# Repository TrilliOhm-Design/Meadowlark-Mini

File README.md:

# Meadowlark-Mini

Dual deploy programable flight computer for amature rocketry. Equipped with a beeper, physical interrupt, battery monitoring, three pyro channels, IMU, and Pressure sensor. The goal is to offer a feature rich controller that can fit inside a 29mm chassis with the creature comforts of modern controllers. The system is powered by an ESP32-C6 microcontroller.  

### Hardware Specs
* 10 to 1200 mbar operating range 
* +/- 2.5 mbar pressure error band
* +/- 0.012 mbar relative pressure accuracy
* +/- 32g accelerometer range
* +/- 2000 dps gyroscope
* embedded temperature compensation
* ~35mA operating consumption 
* Buzzer 80db
* 3 pyro channels
* Stable power supply (3-17V)

### Testing
- [x] Hardware validation
- [x] Firmware Initialized
- [ ] Test Functionallity
        - [x] Indicator light
        - [x] Pyro circuit
        - [x] Buzzer
        - [x] Pressure sensor
        - [x] IMU
        - [ ] Flight logs
        - [ ] HighPower supply
- [ ] Software endurance test
- [ ] Simulated flight test
- [ ] Passenger flight tests (collect data and tune triggers)
- [ ] Flight as main controller
- [ ] Flight as secondary controller

Repeat any tests until the controller passes with reliable behavior.

# Hardware

The board is laid out such it has pyro channels on top and bottom. With two pyro channels on one side and an enable pin on the other. On the other side of the board you have a JST PH connector for power input from a 2s battery. 

I also wanted easy mounting so the board is mounted using two M3 screws.
### [Hardware Details](https://github.com/colinhalebrown/Meadowlark-Mini/tree/main/Hardware)

# Software

The board is equipped with WIFI, Bluetooth, LoRa and Zigbee. The ESP32-C6 has a built in antenna and a u.FL plug that the user can switch between. 

### Pinout
| System          | Signal Type    | Label    | GPIO         | Verified |
| --------------- | -------------- | -------- | ------------ | -------- |
| Indicator LED   | Digital Output | D13      | GPIO13       | Y        |
| Buzzer          | Digital Output | A0       | GPIO26       | Y        |
| Battery Monior  | Analog Input   | A1       | AD1          | Y        |
| Pyro 1          | Digital Output | D12      | GPIO12       | Y        |
| Pyro 2          | Digital Output | D3       | GPIO6        | Y        |
| Pyro 3          | Digital Output | D6       |              | Y        |
| Pressure Sensor | I2C            | SDA, SCL | GPIO2, GPIO3 | Y        |
| IMU             | I2C            | SDA, SCL | GPIO2, GPIO3 | Y        |

# Status
Currently the board needs software so it can get tested in flight as a payload.

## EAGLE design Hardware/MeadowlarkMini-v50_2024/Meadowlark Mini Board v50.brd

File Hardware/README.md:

# Meadowlark-Mini Hardware

### Known Issues
* none

Boards have paste added using a stencil

Components are added to the board by hand 

The board is then baked and the solder joints inspected. Board tested for shorts. After testing the board either needs rework or is cleared for a microcontroller. The controller and power plug are soldiered by hand to the bottom.

The boards are then tested and conformal coated once all rework as been completed. Ports, Plugs, buttons, and sensors are avoided to prevent loss of functionality. 

The enclosure was removed to save weight and allow for users to incorporate the board into their AV bays easier.

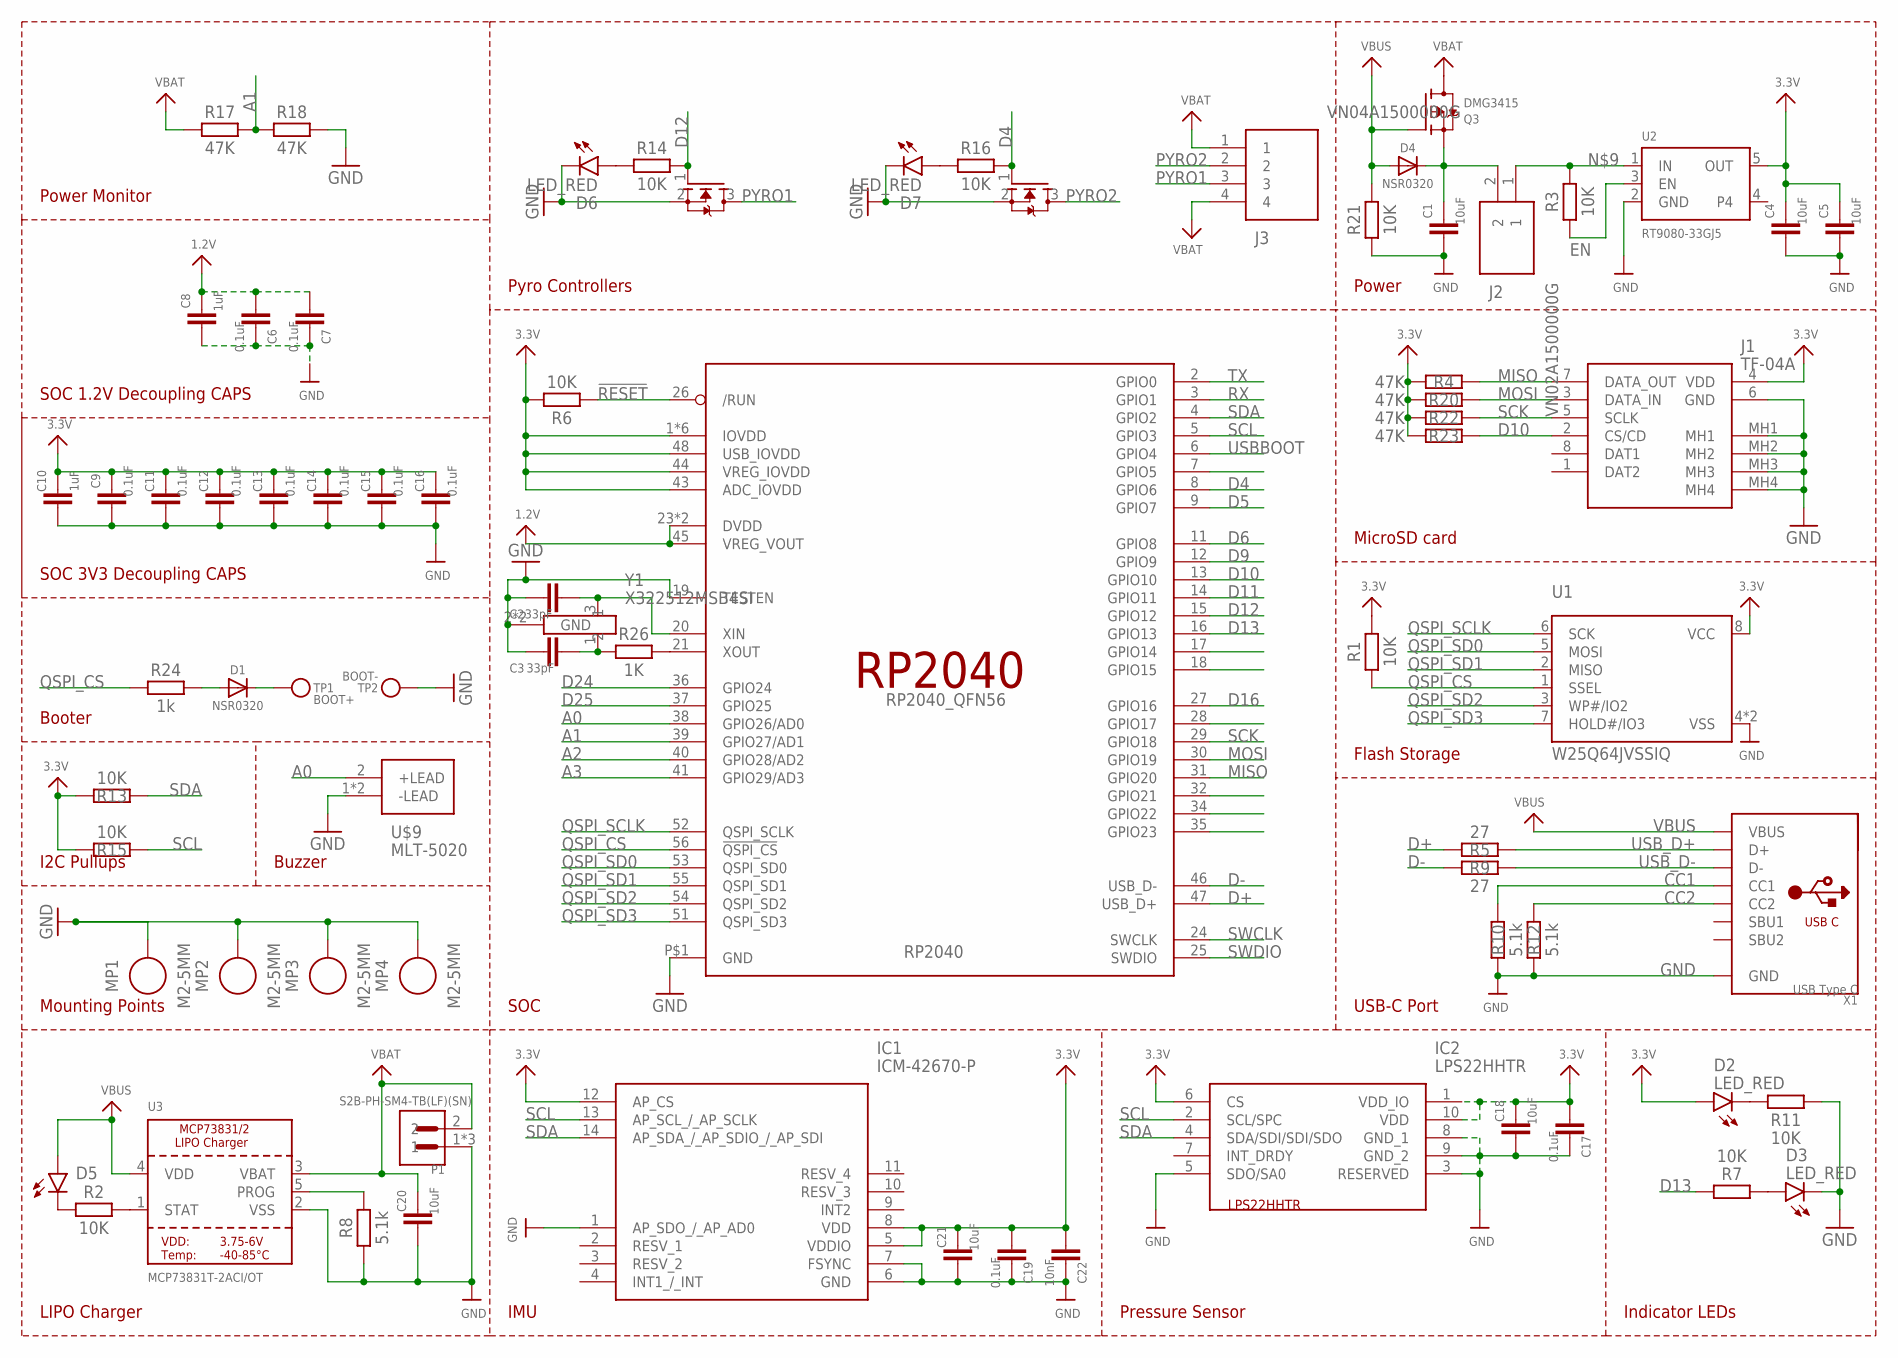
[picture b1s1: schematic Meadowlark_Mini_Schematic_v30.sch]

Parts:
C1, C4, C5, C18, C20, C21: 10uF; CAPC1005X60
C2, C3: 33pF; CAPC1005X60
C6, C7, C9, C11, C12, C13, C14, C15, C16, C17, C19: 0.1uF; CAPC1005X60
C8, C10: 1uF; CAPC1005X60
C22: 10nF; CAPC1005X60
D1, D4: NSR0320; SOD-323_MINI
D2, D3, D6, D7: LED_RED; LEDC1608X55N_FLAT-R
D5: LED_YELLOW; LEDC1608X55N_FLAT-Y
IC1: ICM-42670-P; ICM42670P
IC2: LPS22HHTR
J1: TF-04A; TF04A
J2: VN02A1500000G
J3: VN04A1500000G
MP1, MP2, MP3, MP4: M2-5MM; STANDOFF_HEX_MALE-FEMALE_400X500_M2X0.4_MTGP600H220
P1: S2B-PH-SM4-TB(LF)(SN); JST_S2B-PH-SM4-TB(LF)(SN)
Q1, Q2: AO3400A; SOT23-WIDE
Q3: DMG3415; SOT23-R
R1, R2, R3, R6, R7, R11, R13, R14, R15, R16, R21: 10K; RESC1005X40
R4, R17, R18, R20, R22, R23: 47K; RESC1005X40
R5, R9: 27; RESC1005X40
R8, R10, R12: 5.1k; RESC1005X40
R24: 1k; RESC1005X40
R26: 1K; RESC1005X40
RP2040: RP2040_QFN56; QFN56_7MM_REDUCEDEPAD
TP1: BOOT+; TESTPOINT_ROUND_1.5MM_NO
TP2: BOOT-; TESTPOINT_ROUND_1.5MM_NO
U1: W25Q64JVSSIQ; USON8_4X4
U2: RT9080-33GJ5; SOT23-5; JLC_ROTATION 0
U3: MCP73831T-2ACI/OT; SOT23-5
U$9: MLT-5020; MLT5020
X1: USB Type C; USB_C_CUSB31-CFM2AX-01-X
Y1: X322512MSB4SI

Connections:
1.2V: C6.2, C7.2, C8.1, RP2040.23 (DVDD), RP2040.45 (VREG_VOUT), RP2040.50 (DVDD)
3.3V: C4.1, C5.1, C9.1, C10.1, C11.1, C12.1, C13.1, C14.1, C15.1, C16.1, C17.2, C18.1, C19.2, C21.1, C22.2, D2.A, IC1.5 (VDDIO), IC1.8 (VDD), IC1.12 (AP_CS), IC2.1 (VDD_IO), IC2.6 (CS), IC2.10 (VDD), J1.4 (VDD), R1.2, R4.1, R6.2, R13.2, R15.2, R20.1, R22.1, R23.1, RP2040.1 (IOVDD), RP2040.10 (IOVDD), RP2040.22 (IOVDD), RP2040.33 (IOVDD), RP2040.42 (IOVDD), RP2040.43 (ADC_IOVDD), RP2040.44 (VREG_IOVDD), RP2040.48 (USB_IOVDD), RP2040.49 (IOVDD), U1.8 (VCC), U2.5 (OUT)
!RESET: R6.1, RP2040.26 (/RUN)
A0: RP2040.38 (GPIO26/AD0), U$9.2 (+LEAD)
A1: R17.2, R18.1, RP2040.39 (GPIO27/AD1)
A2: RP2040.40 (GPIO28/AD2)
A3: RP2040.41 (GPIO29/AD3)
CC1: R10.2, X1.A5 (CC1)
CC2: R12.2, X1.B5 (CC2)
D4: Q2.1 (G), R16.2, RP2040.8 (GPIO6)
D5: RP2040.9 (GPIO7)
D6: RP2040.11 (GPIO8)
D9: RP2040.12 (GPIO9)
D10: J1.2 (CS/CD), R23.2, RP2040.13 (GPIO10)
D11: RP2040.14 (GPIO11)
D12: Q1.1 (G), R14.2, RP2040.15 (GPIO12)
D13: R7.2, RP2040.16 (GPIO13)
D16: RP2040.27 (GPIO16)
D24: RP2040.36 (GPIO24)
D25: RP2040.37 (GPIO25)
D+: R5.1, RP2040.47 (USB_D+)
D-: R9.1, RP2040.46 (USB_D-)
EN: R3.1, U2.3 (EN)
GND: C1.2, C2.1, C3.1, C4.2, C5.2, C6.1, C7.1, C8.2, C9.2, C10.2, C11.2, C12.2, C13.2, C14.2, C15.2, C16.2, C17.1, C18.2, C19.1, C20.2, C21.2, C22.1, D3.C, D6.C, D7.C, IC1.1 (AP_SDO_/_AP_AD0), IC1.6 (GND), IC1.7 (FSYNC), IC2.3 (RESERVED), IC2.5 (SDO/SA0), IC2.8 (GND_1), IC2.9 (GND_2), J1.6 (GND), J1.MH1, J1.MH2, J1.MH3, J1.MH4, MP1.1, MP2.1, MP3.1, MP4.1, P1.1, P1.P1 (1), P1.P2 (1), Q1.2 (S), Q2.2 (S), R8.1, R10.1, R11.2, R12.1, R18.2, R21.1, RP2040.19 (TESTEN), RP2040.P$1 (GND), TP2.P$1, U1.4 (VSS), U1.PAD (VSS), U2.2 (GND), U3.2 (VSS), U$9.1 (-LEAD), U$9.3 (-LEAD), X1.A1B12 (GND), X1.B1A12 (GND), Y1.2 (GND), Y1.4 (GND)
MISO: J1.7 (DATA_OUT), R4.2, RP2040.31 (GPIO20)
MOSI: J1.3 (DATA_IN), R20.2, RP2040.30 (GPIO19)
unnamed: D5.C, R2.1
unnamed: D2.C, R11.1
unnamed: R2.2, U3.1 (STAT)
unnamed: R8.2, U3.5 (PROG)
unnamed: D6.A, R14.1
unnamed: C3.2, R26.1, Y1.1
unnamed: R26.2, RP2040.21 (XOUT)
unnamed: D1.A, R24.2
unnamed: J2.1, R3.2, U2.1 (IN)
unnamed: D3.A, R7.1
unnamed: D7.A, R16.1
unnamed: C2.2, RP2040.20 (XIN), Y1.3 (2)
PYRO1: J3.3, Q1.3 (D)
PYRO2: J3.2, Q2.3 (D)
QSPI_CS: R1.1, R24.1, RP2040.56 (!QSPI_CS), U1.1 (SSEL)
QSPI_SCLK: RP2040.52 (QSPI_SCLK), U1.6 (SCK)
QSPI_SD0: RP2040.53 (QSPI_SD0), U1.5 (MOSI)
QSPI_SD1: RP2040.55 (QSPI_SD1), U1.2 (MISO)
QSPI_SD2: RP2040.54 (QSPI_SD2), U1.3 (WP#/IO2)
QSPI_SD3: RP2040.51 (QSPI_SD3), U1.7 (HOLD#/IO3)
RX: RP2040.3 (GPIO1)
SCK: J1.5 (SCLK), R22.2, RP2040.29 (GPIO18)
SCL: IC1.13 (AP_SCL_/_AP_SCLK), IC2.2 (SCL/SPC), R15.1, RP2040.5 (GPIO3)
SDA: IC1.14 (AP_SDA_/_AP_SDIO_/_AP_SDI), IC2.4 (SDA/SDI/SDI/SDO), R13.1, RP2040.4 (GPIO2)
SWCLK: RP2040.24 (SWCLK)
SWDIO: RP2040.25 (SWDIO)
TX: RP2040.2 (GPIO0)
USBBOOT: D1.C, RP2040.6 (GPIO4), TP1.P$1
USB_D+: R5.2, X1.A6 (D+), X1.B6 (D+)
USB_D-: R9.2, X1.A7 (D-), X1.B7 (D-)
VBAT: C20.1, J3.1, J3.4, P1.2, Q3.3 (D), R17.1, U3.3 (VBAT)
VBUS: D4.A, D5.A, Q3.1 (G), R21.2, U3.4 (VDD), X1.A4B9 (VBUS), X1.B4A9 (VBUS)
VHI: C1.1, D4.C, J2.2, Q3.2 (S)

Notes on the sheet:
Power
LIPO Charger
MicroSD card
Flash Storage
USB-C Port
SOC
Pyro Controllers
IMU
Pressure Sensor
I2C Pullups
Indicator LEDs
Mounting Points
Buzzer
Booter
SOC 3V3 Decoupling CAPS
SOC 1.2V Decoupling CAPS
Power Monitor

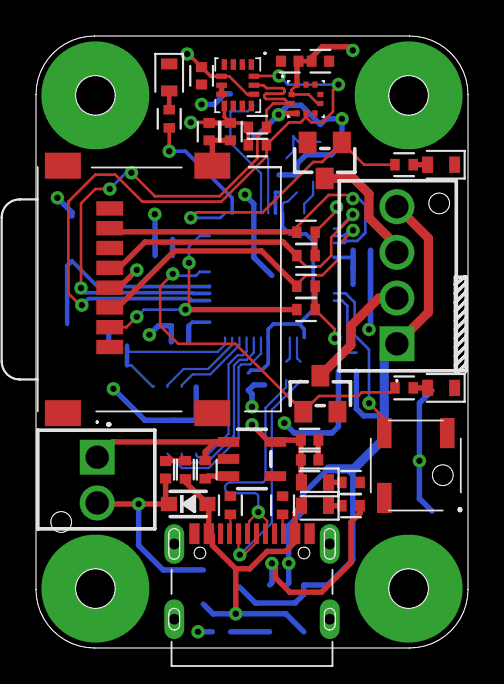
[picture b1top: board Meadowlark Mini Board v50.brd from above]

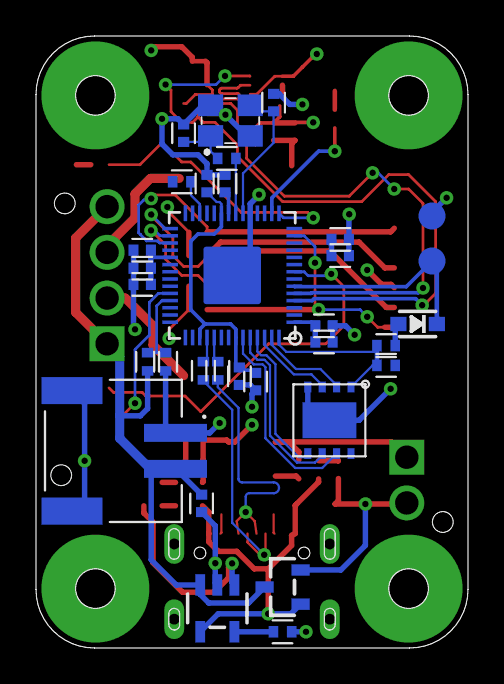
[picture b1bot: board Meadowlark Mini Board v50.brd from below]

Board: 2 copper layers, 24.0 x 34.0 mm, 75 parts (32 on the bottom side), 46 nets.

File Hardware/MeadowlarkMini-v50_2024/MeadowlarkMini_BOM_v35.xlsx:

Meadowlark Mini BOM
Comment | Designator | Footprint | Part # |  | URL | QTY | Type | Notes
MLT-5020 | U$9 | MLT5020 | C94598 |  | JLC | 1 | Extended | Buzzer
S2B-PH-SM4-TB | P1 | JST_S2B-PH-SM4-TB(LF)(SN) | C295747 |  | JLC | 1 | Extended | JST-PH 2P
RP2040 | RP2040 | QFN56_7MM_REDUCEDEPAD | C2040 |  | JLC | 1 | Extended | RP2040 SOC
TF-04A | J1 | TF04A | C145799 |  | JLC | 1 | Extended | MicroSD Slot
DB125-2.54-4P-GN-S | J3 | VN04A1500000G | C918122 |  | JLC | 1 | Extended | 4P 2.54mm Screw
DB301V-3.5-2P-GN-S | J2 | VN02A1500000G | C918120 |  | JLC | 1 | Extended | 2P 2.54mm Screw
W25Q64JVXGIQ | U1 | USON8_4X4 | C2940195 |  | JLC | 1 | Extended | Flash Storage
ICM-42670-P | IC1 | ICM42670P | C3288646 |  | JLC | 1 | Extended | IMU
LPS22HHTR | IC2 | LPS22HHTR | C2827824 |  | JLC | 1 | Extended | Barometer
SI2301CDS-T1-GE3 | Q3 | SOT23-R | C10487 |  | JLC | 1 | Basic | Power MOSFET
RT9080-33GJ5 | U2 | SOT23-5 | C841192 |  | JLC | 1 | Extended | Voltage regulator
MCP73831T-2ACI/OT | U3 | SOT23-5 | C424093 |  | JLC | 1 | Extended | LIPO Charger
TYPE-C 16PIN 2MD(073) | X1 | USB_C_CUSB31-CFM2AX-01-X | C2765186 |  | JLC | 1 | Extended | USB-C port
AO3400A | Q1, Q2 | SOT23-WIDE | C20917 |  | JLC | 2 | Basic | Load MOSFET
0402WGF1001TCE | R24, R26 | RESC1005X40 | C11702 |  | JLC | 2 | Basic | 1k 0402
1N5819WS | D1, D4 | SOD-323_MINI | C191023 |  | JLC | 2 | Basic | Original Part
0402WGF1002TCE | R1, R2, R3, R6, R7, R11, R13, R14, R15, R16, R21 | RESC1005X40 | C25744 |  | JLC | 13 | Basic | 10k 0402
CL05A106MQ5NUNC | C1, C4, C5, C18, C20, C21 | CAPC1005X60 | C15525 |  | JLC | 6 | Basic | 10uF 0402
CL05B104KB54PNC | C6, C7, C9, C11, C12, C13, C14, C15, C16, C17, C19 | CAPC1005X60 | C307331 |  | JLC | 11 | Basic | 0.1uF 0402
CL05B103KB5NNNC | C22 | CAPC1005X60 | C15195 |  | JLC | 1 | Basic | 10nF 0402
KT-0603R | D2, D3, D6, D7 | LEDC1608X55N_FLAT-R | C2286 |  | JLC | 4 | Basic | Red LED 0603
19-213/Y2C-CQ2R2L/3T(CY) | D5 | LEDC1608X55N_FLAT-Y | C72038 |  | JLC | 1 | Basic | Yellow LED 0603
0402WGF5101TCE | R8, R10, R12 | RESC1005X40 | C25905 |  | JLC | 3 | Basic | 5.1k 0402
0402WGF4702TCE | R4, R17, R18, R20, R22, R23 | RESC1005X40 | C25792 |  | JLC | 6 | Basic | 47k 0402
0402CG330J500NT | C2, C3 | CAPC1005X60 | C1562 |  | JLC | 2 | Basic | 33pF 0402
X322512MSB4SI | Y1 | X322512MSB4SI | C9002 |  | JLC | 1 | Basic | Clock Cystal
CL05A105KA5NQNC | C8, C10 | CAPC1005X60 | C52923 |  | JLC | 2 | Basic | 1uF 0402
0402WGF270JTCE | R5, R9 | RESC1005X40 | C25100 |  | JLC | 2 | Extended | 27 0402

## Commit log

2026-04-03 Code and board updates
2026-04-06 Update Flight_TestCode_v0.33.ino
    Updated and added some comments
2026-06-03 update flight code
2026-06-04 Add Hardware Licence
2026-06-04 Reorganize Hardware Files
2026-06-04 Add updated hardware
2026-06-10 initial dev env
2026-06-10 create inital dev container
2026-06-10 fix extension problems
2026-06-10 update libraries
2026-06-10 move .claude so it doesn't get included in build
2026-06-10 intellisense build succesful
2026-06-10 update documentation
2026-06-10 initial poc
2026-06-10 update container readme
2026-06-10 force intellisense engine to use default

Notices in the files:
parts and their libraries:
microbuilder: This work is placed in the public domain, and may be freely used for commercial and non-commercial work with the following conditions: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
